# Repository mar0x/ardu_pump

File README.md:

# ardu_pump
Attiny45-based ultrasonic automatic water pump controller.

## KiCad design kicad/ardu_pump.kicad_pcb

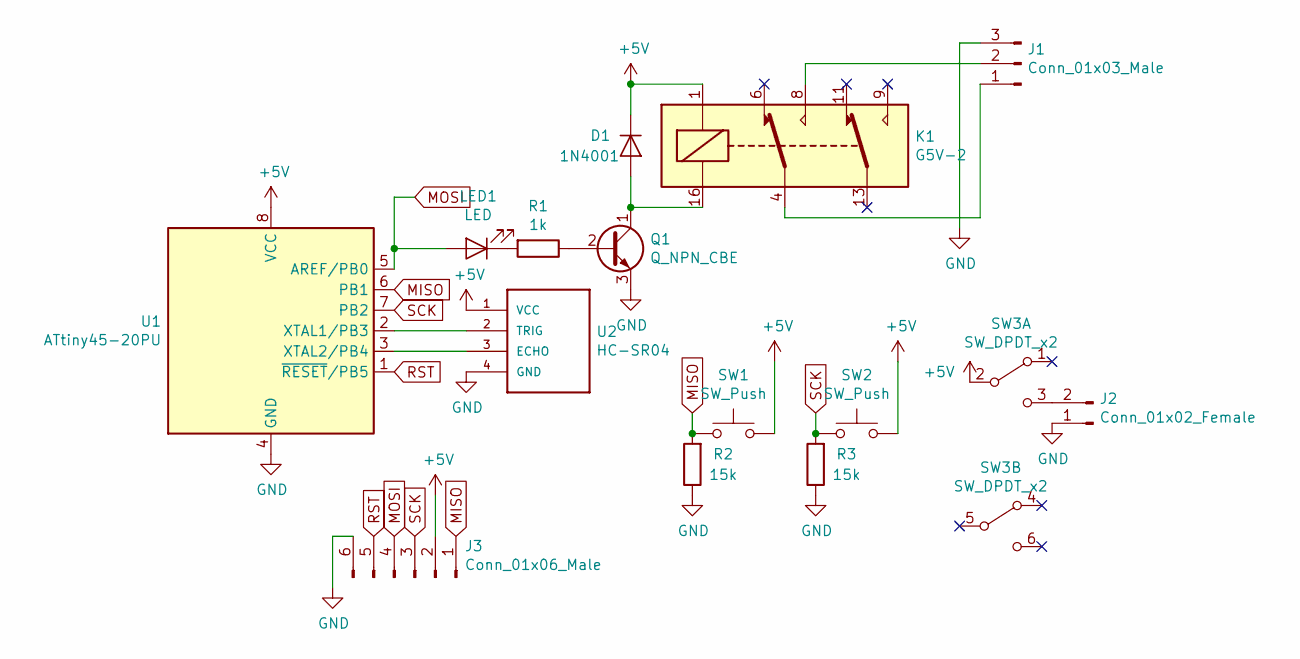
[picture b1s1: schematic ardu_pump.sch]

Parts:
D1: 1N4001; D_A-405_P7.62mm_Horizontal
J1: Conn_01x03_Male; JST_XH_S03B-XH-A_1x03_P2.50mm_Horizontal
J2: Conn_01x02_Female; JST_XH_B02B-XH-A_1x02_P2.50mm_Vertical
J3: Conn_01x06_Male; IDC-Header_2x03_P2.54mm_Vertical
K1: G5V-2; Relay_DPDT_Omron_G5V-2
LED1: LED; LED_D3.0mm
Q1: Q_NPN_CBE; TO-92_Inline_Wide
R1: 1k; R_Axial_DIN0207_L6.3mm_D2.5mm_P15.24mm_Horizontal
R2, R3: 15k; R_Axial_DIN0207_L6.3mm_D2.5mm_P7.62mm_Horizontal
SW1, SW2: SW_Push; SW_Tactile_SPST_Angled_PTS645Vx58-2LFS
SW3: SW_DPDT_x2; SW_PUSH_8x8mm_DPDT
U1: ATtiny45-20PU; DIP-8_W7.62mm
U2: HC-SR04; PinSocket_1x04_P2.54mm_Horizontal

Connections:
+5V: D1.1 (K), J3.2, K1.1, SW1.2, SW2.2, SW3.2 (B), U1.8 (VCC), U2.1 (VCC)
GND: J1.3, J2.1, J3.6, Q1.3 (E), R2.1, R3.1, U1.4 (GND), U2.4 (GND)
MISO: J3.1, R2.2, SW1.1, U1.6 (PB1)
MOSI: J3.4, LED1.2 (A), U1.5 (AREF/PB0)
unnamed: D1.2 (A), K1.16, Q1.1 (C)
unnamed: J1.1, K1.4
unnamed: J1.2, K1.8
unnamed: J2.2, SW3.3 (C)
unnamed: LED1.1 (K), R1.2
unnamed: Q1.2 (B), R1.1
unnamed: U1.2 (XTAL1/PB3), U2.2 (TRIG)
unnamed: U1.3 (XTAL2/PB4), U2.3 (ECHO)
RST: J3.5, U1.1 (~RESET~/PB5)
SCK: J3.3, R3.2, SW2.1, U1.7 (PB2)

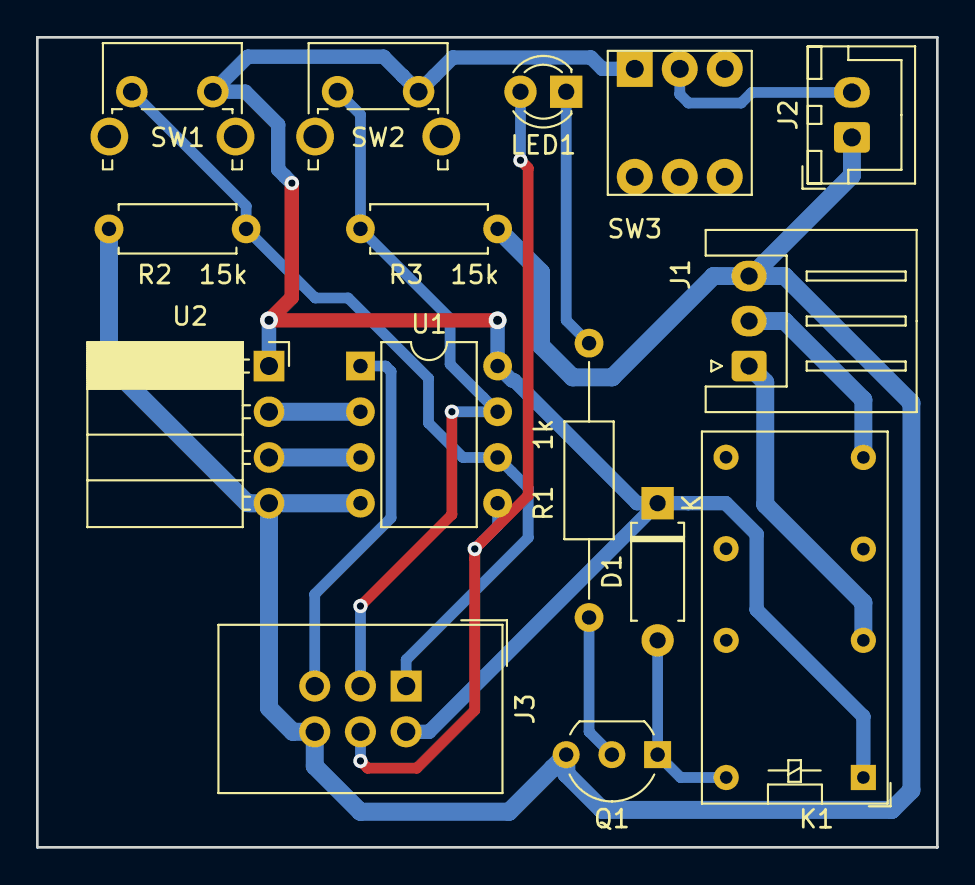
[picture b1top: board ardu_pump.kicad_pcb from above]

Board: 2 copper layers, 50.0 x 45.0 mm, 15 parts (0 on the bottom side), 14 nets.

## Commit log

2019-03-07 Initial commit.
2019-03-07 Image.
2019-03-07 Creating README.md
2019-03-22 Introducing KiCad files.
2019-03-22 Power saving attempts.
2019-03-22 Fixing typo.
2019-03-23 Improving schematic.
    Adding buttons and more powerful relay.
